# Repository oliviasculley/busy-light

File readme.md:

# Busy Light

This repo contains the schematics, PCB files and media for a synced busy-light
control box that can be used to communicate up to 5 states, indicated with LEDs.
The wireless communication is fault-tolerant and utilizes encrypted ESP-NOW for
communication, which means that it doesn't have any other dependencies besides
power and your communications are secure!

## Schematic and PCB

## Components

- [22mm 3x Control box](https://www.aliexpress.us/item/3256805247196863.html)
- [Red, Yellow and Green buttons](https://www.aliexpress.us/item/3256803827064988.html)
- [Button connector leads](https://www.aliexpress.us/item/3256803827064988.html)
- [LED Status Lights](https://www.aliexpress.us/item/2251832784127555.html)
- [Through-hole resistors](https://www.aliexpress.us/item/3256807885719870.html)
- [Wemos D1 Mini ESP 8266](https://www.amazon.com/dp/B081PX9YFV)
- [USB power brick](https://www.amazon.com/dp/B08H5421TJ)
- [Micro-USB cable](https://www.amazon.com/dp/B0D7RZJSPS)

Estimated part costs (without shipping):
- Two 22mm 3x Control boxes: $6.62
- Red, Yellow and Green buttons and connector leads: $20.76
- LED Status Lights: $5.34
- Wemos D1 Mini ESP 8266s: $12.98
- Through-hole resistors: $2.68
- USB power bricks: $11.99
- Micro-USB cables: $5.49

Estimated Total: around $66 for 2 boxes, or around $33 each

## Tools required

- Screwdriver
- Small eyeglasses screwdriver
- Soldering iron
- Solder
- Solid core wires
- Wire stripper
- Arduino IDE
- Kicad

## Assembly notes

- Use blue and white leads for button switches
- Use 150 ohm resistors for all LEDs
- For the Arduino IDE, you will need the
  [ESP8266 library](https://github.com/esp8266/Arduino) installed
- Epoxy putty around the cable is optional but recommended!
- To order the boards from JLCPCB yourself, visit the releases to download the
  compiled gerber files
- The boards are set to 9600 baud serial
- Use serial to determine the board's mac addresses
- Then, fill in `BROADCAST_ADDRESS[]` with both boards' mac addresses
- Toggle the `#if true` between true and false to flash corresponding boxes
- (Optional) Set a new 16 char encryption key for better security

## Instructions

- The lights in the buttons corresponds to your current state
- The lights next to the buttons corresponds to the other device's state
- Press any button to light up the corresponding light on the other device
- Hold down the red button to light up both yellow and red at the same time
- Hold down the green button to turn off all lights
- The green status lights will automatically shut off after 6 hours in the green status

## Repository structure
- `busy-light-1.0.0/` contains the original prototypes I made with protoboards
- `busy-light-1.1.0/` contains the fabbed version of the board
  - There's not enough clearance for the micro-USB cable, so you will have to file
    down the head of the cable or find a lower-profile connection
  - Getting the stranded-core wires through the holes is really annoying, I need
    to make the holes a bit bigger
- `busy-light-1.2.0/` contains a new version that hasn't been fabbed yet and has
  the following changes:
  - Bigger holes for stranded-core wires
  - SMD resistors
  - Flipped ESP8266 for better cable clearance
  - More efficient board 😄

## Potential future changes
- Find a better connecting solution for the stranded core wires, maybe turrent
  terminals or something
- Add mounting for PCB (Mounting holes?)
- Add mounting for Micro-USB cable
- Use FreeRTOS if I feel like writing a lot of boilerplate
- CAD an 3D printable enclosure to use instead

## Project Log

1. The first prototype boards
   
1. Soldering the resistors
   
1. Wrapping wires around pins
   
1. Trimmed wires
   
1. Wired up prototype boards. Do you see the mistake?
   
1. Adding screw terminals
   
1. Fixing my mistake (Please excuse the soldering, most of this project was done
   after midnight 😅😅😅) 
1. Wiring up buttons and lights
   
1. Installing switches into control boxes
   
1. Adding a pull-up resistor to pin D0. Turns out that the ESP8266 doesn't have
   a usable internal pull-up on D0. Something to keep in mind!
   
1. The boxes mid-assembly!
   
1. Filling the end-caps with epoxy putty
   
1. An early version of the PCB board

1. A 3D view of an early version of the PCB board
   
1. A 3D view of an early version of just the PCB board
   
1. A 3D view of another revision of the PCB board
   
1. A 3D view of the v1.1.0 revision of just the PCB board
   
1. The final working prototypes (Not using the fabbed boards)
   
1. The fabbed boards! My logo in the silkscreen came out great!
   
1. Doing some cable management
   
1. The fabbed boards work!
   
1. A view of all the wires to the PCB
   
1. Trimming the leads on the back of the PCB

## Misc Notes

- Vf red led button: 1.87v @ 3.4v
- Vf yellow led button: 2.58v @ 3.5v
- Vf green led button: 2.54v @ 3.6v

---

- Vf red: 1.84v @ 3.7v
- Vf yellow: 1.92v @ 3.8v
- Vf green: 2.30v @ 4.0v

---

- (3 - 1.85) / 20 (milliamps) * 1000 = 57 ohm
- (3 - 2.6) / 20 (milliamps) * 1000 = 20 ohm
- (4 - 1.85) / 20 (milliamps) * 1000 = 108 ohm
- (4 - 2.6) / 20 (milliamps) * 1000 = 70 ohm
- 150 ohm resistors seem good enough

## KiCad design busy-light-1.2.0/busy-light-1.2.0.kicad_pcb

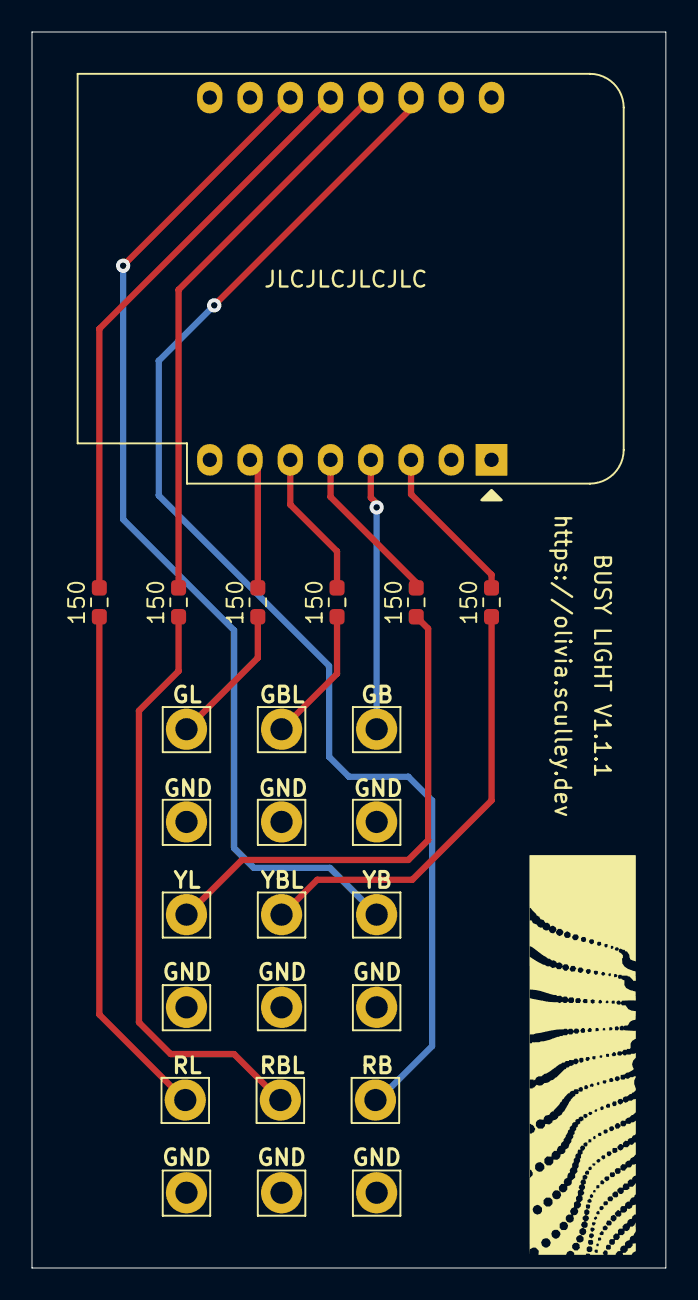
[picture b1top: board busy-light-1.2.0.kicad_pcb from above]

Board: 4 copper layers, 40.0 x 78.0 mm, 25 parts (1 on the bottom side), 16 nets.

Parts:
J1, J2, J3, J4, J5, J6, J7, J8, J9, J10, J11, J12, J13, J14, J15, J16, J17, J18: Conn_01x01_Pin; Pin_D1.4mm_L8.5mm_W2.8mm_FlatFork
R1, R2, R3, R4, R5, R6: 150; R_0603_1608Metric_Pad0.98x0.95mm_HandSolder
U1: WEMOS_D1_mini; WEMOS_D1_mini_light

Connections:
/GREEN BUTTON: J17.1, U1.4 (SCK/D5)
/GREEN BUTTON LIGHT: R1.1, U1.6 (MOSI/D7)
/GREEN BUTTON LIGHT CONN: J15.1, R1.2
/GREEN LIGHT: R6.1, U1.7 (CS/D8)
/GREEN LIGHT CONN: J13.1, R6.2
/RED BUTTON: J5.1, U1.14 (SCL/D1)
/RED BUTTON LIGHT: R3.1, U1.13 (SDA/D2)
/RED BUTTON LIGHT CONN: J3.1, R3.2
/RED LIGHT: R4.1, U1.12 (D3)
/RED LIGHT CONN: J1.1, R4.2
/YELLOW BUTTON: J11.1, U1.11 (D4)
/YELLOW BUTTON LIGHT: R2.1, U1.3 (D0)
/YELLOW BUTTON LIGHT CONN: J9.1, R2.2
/YELLOW LIGHT: R5.1, U1.5 (MISO/D6)
/YELLOW LIGHT CONN: J7.1, R5.2
GND: J2.1, J4.1, J6.1, J8.1, J10.1, J12.1, J14.1, J16.1, J18.1, U1.10 (GND)

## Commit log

2025-03-20 remove board design screenshot
2025-03-20 add PCB image at top
2025-03-23 add v1.1.1
2025-04-05 add more pictures
2025-04-05 add bugs with revision
2025-04-06 rename to 1.2.0
2025-04-13 reset lights by holding down green button
2025-07-17 add extended shutoff mechanism
